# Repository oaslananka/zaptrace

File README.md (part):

<div align="center">

# ⚡ ZapTrace

### AI-native, verification-first EDA kernel for prompt-to-fab electronics.

**Prompt-to-Fab, with proofs.**<br />
Intent → normalized design → schematic → ERC → placement → routing → DRC → BOM → manufacturing package → auditable proof pack.

<p>

</p>

<p>

</p>

<p>
  <a href="https://oaslananka.github.io/zaptrace"><strong>Documentation</strong></a> ·
  <a href="#quickstart">Quickstart</a> ·
  <a href="docs/development/validation-environment.md">Validation Environment</a> ·
  <a href="ROADMAP.md">Roadmap</a> ·
  <a href="GOVERNANCE.md">Governance</a> ·
  <a href="SECURITY.md">Security</a> ·
  <a href="docs/SAFETY.md">Safety</a>
</p>

<p>
  
</p>

</div>

> [!WARNING]
> **Pre-1.0.** ZapTrace is a verification-first EDA kernel, not a fabrication guarantee. All generated outputs require human engineering review before fabrication or use. See [Safety Disclaimer](#safety-disclaimer).

> [!NOTE]
> **Proof Pack = evidence layer, not absolute correctness.** Proof packs record configured checks, artifacts, assumptions, and pass/fail evidence. A clean proof pack does not mean a board is manufacturer-approved, production-ready, or safe to fabricate without review.

---

## What ZapTrace Is

- **A Python SDK** for programmatic electronics design — parse, validate, place, route, export.
- **A CLI** (`zaptrace`) for quick design iteration from the terminal.
- **A local-first visual Studio** (`zaptrace studio`) for source-driven circuit exploration, linked component selection, preliminary board placement and safe YAML editing; not yet a full professional PCB CAD editor.
- **An MCP server** (`zaptrace-mcp`) whose default `expert` surface exposes 93 design tools plus 3 session-administration tools, with smaller task-oriented `inspect`, `design`, `verify`, `repair`, and `release` surfaces for bounded workflows.
- **A REST API** for web-based design workflows.
- **A verification engine** — Electrical Rule Checking (ERC) + Design Rule Checking (DRC) baked in.
- **A manufacturing export pipeline** — Gerber RS-274X, Excellon drill, BOM, pick-and-place, KiCad.
- **A proof-pack generator** — auditable, reproducible artifact bundles for every design.

## What ZapTrace Is Not

- ❌ **Not a full replacement for KiCad, Altium, or Eagle** — the initial Studio provides a live source and provisional-placement workspace, not full native CAD editing or manufacturing approval.
- ❌ **Not a general-purpose SPICE simulator or solver-grade sign-off tool** — ZapTrace can export SPICE and run bounded ngspice-backed evidence gates, but these do not replace full analog verification or qualified engineering review.
- ❌ **Not a replacement for human engineering judgment** — all outputs require review before fabrication.
- ❌ **Not fabrication-proven** — ZapTrace is pre-1.0. Manufacturing outputs are experimental.
- ❌ **Not fabrication-ready or production-ready** — no claim of fitness for manufacturing is made.
- ❌ **Proof Pack is not a correctness guarantee** — it is an evidence layer that records what was checked and what passed/failed. Absence of errors does not mean the design is correct or manufacturable.
- ❌ **KiCad Oracle (ERC/DRC) is external validation, not absolute correctness** — it catches rule violations the rules know about. A passing KiCad Oracle check does not guarantee a working circuit.
- ❌ **Fab profiles are not manufacturer approvals** — built-in profiles match common manufacturer capabilities, but you must verify against your specific manufacturer's current specifications. Always obtain pre-fabrication approval.
- ❌ **GitHub hardware CI cannot catch all hardware errors** — CI runs on simulated or limited hardware; physical validation (probe, power-up, functional test) is irreplaceable.

---

## Status

| Area | Status |
|------|--------|
| Design parsing | ✅ Implemented |
| Schematic synthesis | ⚠️ Template selection (keyword-matches a pre-built template; not from-scratch synthesis) |
| ERC (Electrical Rule Checking) | ✅ Implemented |
| Component placement | ✅ Implemented |
| Grid-based routing | ✅ Implemented |
| Net-aware smart routing | ✅ Implemented |
| DRC (Design Rule Checking) | ✅ Implemented |
| Net classification (EE knowledge) | ✅ Implemented |
| Copper pour generation | ✅ Implemented |
| Gerber RS-274X export | ✅ Implemented |
| Excellon drill export | ✅ Implemented |
| BOM (CSV + JSON) export | ✅ Implemented |
| Pick-and-place export | ✅ Implemented |
| KiCad schematic export | ✅ Implemented |
| KiCad hierarchical project import | ✅ Implemented |
| EasyEDA Standard import/export (round-trip ≥0.75) | ✅ Implemented (single flat JSON; import-only, no PCB editor) |
| EasyEDA Pro writer (import-only via KiCad) | ✅ Implemented (ZIP+JSONL; distinct from Standard) |
| Altium ASCII schematic import | ✅ Implemented (ASCII export only; OLE binary not supported) |
| SVG schematic rendering | ✅ Implemented |
| Manufacturing ZIP bundle | ✅ Implemented |
| MCP server (96 exposed tools: 93 design + 3 session administration) | ✅ Implemented |
| Power-tree architecture planner + netlist emit | ✅ Implemented |
| REST API server | ✅ Implemented |
| Design diff | ✅ Implemented |
| Full pipeline (autopilot) | ✅ Implemented |
| Proof-pack system | ✅ Implemented — evidence/sign-off foundation; not a correctness guarantee |
| Plugin system | 🚧 Experimental — signed runtime policy documented; production sandboxing still required |
| Review Studio | ✅ Implemented — human-review panels, proof-pack evidence, benchmark readiness |
| Live Code-to-Circuit Studio | 🧪 Initial local browser workspace — real YAML editing, source-linked connectivity/placement preview, save/undo and agent-aware revision tracking; native schematic editing and production CAD not yet supported |
| SPICE netlist export | ✅ Implemented foundation — DC gate is evidence/skip aware, not full analog sign-off |
| DFM (Design for Manufacturing) | ✅ Implemented foundation — fab profiles, manufacturing evidence, current/thermal/SI risk reports |
| Multi-board design | 🔮 Planned — post-0.3.0 |
| RF/microwave awareness | 🔮 Planned |

---

## v0.3.0 Release Scope

ZapTrace 0.3.0 is an evidence-hardening release. It adds bounded autonomous sign-off vocabulary, requirements coverage, assumption evidence, KiCad oracle evidence, manufacturing/DFM evidence, component/datasheet/footprint provenance, layout/power/SI/PI risk reports, known-failure benchmark mutation coverage, and Review Studio benchmark readiness panels.

This release still makes no fabrication-readiness claim. A pass means the configured evidence gates did not block; it does **not** mean the design is manufacturer-approved, production-ready, or safe to fabricate without human engineering review.

---

## Live Code-to-Circuit Studio

Open a real, editable ESP32 design example in a local browser workspace without manually exporting a static viewer:

**Development builds only for now:** the previously published PyPI 0.3.5 package does not include Studio.

```bash
zaptrace studio

# Or open an existing design.yaml directly (edits affect this file):
zaptrace studio --project path/to/design.yaml
```

Unsaved Studio YAML drafts can be recovered on a tab refresh when the browser retains tab session storage; they are never silently saved to the design file. If an agent changes the YAML while you have unsaved edits, **Compare versions** and **Download my draft** protect your work before you choose to load the agent's version. The **Following your source component** navigator links the selected YAML component to its exact Circuit, Board and illustrative 3D concept object, with keyboard focus and a return-to-source action; it never saves or invents unverified copper. **Double-click a component** in Circuit/Board/3D (or press **F2**) to edit its real YAML value; **Enter/Apply** saves and **Esc** cancels without writing. On first open, the **Start here** guide makes three real actions discoverable: select a source-linked component, trace a genuine net, or import your own YAML copy. It stays out of the way after a choice, is keyboard-accessible, and can be reopened from the header. Once Studio is running, choose **+ Open YAML copy** to select a local design in the browser without typing its path, or **Recent projects** to reopen a saved personal copy. Each import validates the source, opens in its own local session and leaves the original YAML untouched; the imported copy is an independent project, not synchronized back to the original. A running Studio also offers **Recent projects → Add Studio to your apps**, explicitly installing a local Linux Applications or Windows Start menu shortcut for later one-click launches, and **Quit desktop Studio** for app-menu-launched sessions. This uses the installed Python runtime (no Tauri/Electron or additional provider), and does not change desktop settings until clicked. Initial source installation still requires setup. The Studio keeps **one YAML file** as the authoritative design. On systems with KiCad installed, source-mapped resistors and capacitors show genuine local KiCad Device library artwork; selected ESP32/BME280/AMS1117 components can also display verified source-to-library pad matches in Inspector and jump into an interactive native pinout on the Circuit canvas for source-linked pin and net editing. The main Circuit cards also display local, source-matched KiCad ESP32/BME280/AMS1117 symbol artwork when available, with accurate mapped-pad coverage; cold library inspection runs after the fast YAML preview, never as a blocking prerequisite. Missing KiCad libraries keep the safe illustrative fallback. Partial source mappings are clearly reported and never treated as fabrication proof. Edit component values or nets in the code pane and see the corresponding source-linked logical schematic (including two-sided source pins, recognisable passive glyphs, and real net labels) update; select components, inspect source package pad mappings, and highlight logical net links across code and canvas, reassign a logical pin through Inspector or by selecting two schematic pins, trace real source net endpoints, explore board placement by dragging unrouted components, and use **Save design** to persist changes. Invalid drafts retain the last valid visual preview. An external agent/editor edit is detected without silently overwriting unsaved work. Use **↓ KiCad schematic** to download a real KiCad `.kicad_sch` from the current YAML draft (including unsaved net edits), with native KiCad wire segments/global net labels and embedded generated connectivity symbols; this does not save YAML or qualify ERC/DRC. The **3D concept** tab is now a source-linked, selectable isometric placement sketch of the actual board outline and component XY footprints; it does **not** assert native CAD 3D geometry, routed copper or physical validation. For the UI workflow and current engineering limitations, see [Studio user guide](docs/studio.md).

Source-backed pin-to-pin wire paths may now be drawn and adjusted within Studio and exported as real KiCad schematic segments; this is limited route geometry with unqualified generated symbols, not a full native schematic editor or verified copper.\n\nA local visual preview does **not** replace KiCad-native schematic, ERC, DRC, routing verification or qualified fabrication review.

## Quickstart

ZapTrace is pre-1.0. The registry distribution identity is `zaptrace-eda` while the Python import package and CLI remain `zaptrace`. `v0.3.5` is available on PyPI; its immutable tagged workflow failed the container-security gate before GitHub Release creation, so the tag is retained as partial-release evidence rather than rewritten. Active development has advanced to `0.3.6.dev0`. For a clean PyPI install of the latest published package:

```bash
uv venv --python 3.13
uv pip install "zaptrace-eda==0.3.5"
source .venv/bin/activate

# Run diagnostics
zaptrace doctor

# First run: scaffold a design locally (the published wheel does not
# contain the repository's examples/ directory).
zaptrace init sensor-demo --template esp32_i2c_sensor
zaptrace parse sensor-demo/design.yaml
zaptrace view sensor-demo/design.yaml --output sensor-demo/review

# Create KiCad/inspection outputs inside the working directory.
# Generation success does not mean ERC/DRC or fabrication readiness.
zaptrace pipeline --source sensor-demo/design.yaml --output sensor-demo/build
```

---

## CLI Usage

```bash
# Parse a design YAML
zaptrace parse design.yaml

# Inspect a parsed design
zaptrace inspect my_design

# Run ERC validation
zaptrace erc my_design

# List ERC rules
zaptrace erc-rules

# Place components
zaptrace place my_design

# Route nets
zaptrace route my_design

# Generate BOM
zaptrace bom my_design
zaptrace bom my_design --format json

# Generate design report
zaptrace report my_design --output report.md

# Render schematic SVG
zaptrace svg my_design --output schematic.svg

# Export to KiCad
zaptrace kicad my_design output/kicad/

# Diff two designs
zaptrace diff design_a design_b

# Search library
zaptrace library search resistor
zaptrace library get 0402_10k

# Run full pipeline
zaptrace pipeline --source design.yaml --output build/
zaptrace pipeline --intent "ESP32 I2C sensor node"
```

---

## Python SDK Usage

```python
from zaptrace.core.parser import parse_file
from zaptrace.erc.runner import ERCRunner
from zaptrace.algo.placer import place_components
from zaptrace.algo.router import route_design_smart
from zaptrace.export.manufacturing import generate_manufacturing_bundle
from zaptrace.ee.classifier import classify_design

# Parse
design = parse_file("design.yaml")

# Validate
runner = ERCRunner()
erc_result = runner.run(design)

# Classify nets
classify_design(design)

# Place & route
positions = place_components(design)
routing, route_result = route_design_smart(design, positions)

# Export
bundle = generate_manufacturing_bundle(design, "build/")
print(f"Gerber layers: {list(bundle['gerber_layers'].keys())}")
```

---

## MCP Usage

ZapTrace exposes an MCP server for AI agent integration.

```bash
# Start MCP server (stdio mode)
zaptrace-mcp

# Start MCP server (HTTP loopback mode)
zaptrace-mcp-http
```

Configure in your AI client's MCP settings:

```json
{
  "mcpServers": {
    "zaptrace": {
      "command": "zaptrace-mcp"
    }
  }
}
```

See [MCP quickstart](docs/mcp/quickstart.md) for the tool catalog and [agent plugin publication](docs/agent-plugin-publication.md) for product-owned skills, runtime boundaries, and activation gates.

---

## REST API Usage

```bash
# Start the secure loopback server on 127.0.0.1:8080.
zaptrace-api

# Health does not require a bearer token.
curl http://127.0.0.1:8080/health
```

For the authenticated REST and MCP HTTP Compose deployment, copy `.env.example`, set both token values, and run `docker compose up --build --wait`. See [REST API production hardening](docs/api-rest-production.md) and [MCP HTTP deployment](docs/mcp-http-deployment.md).

---

## Manufacturing Export

ZapTrace generates all files needed for PCB fabrication:

| Artifact | Format | Status |
|----------|--------|--------|
| Copper layers | Gerber RS-274X | ✅ |
| Drill file | Excellon | ✅ |
| Bill of Materials | CSV / JSON | ✅ |
| Pick-and-place | CSV | ✅ |
| Manufacturing bundle | ZIP | ✅ |
| KiCad project | .kicad_pcb, .kicad_sch | ✅ |
| Schematic | SVG | ✅ |
| Design report | Markdown | ✅ |

```bash
# Generate everything
zaptrace export manufacturing my_design --output build/board
```

---

## Proof Pack

A Proof Pack is an auditable, reproducible artifact bundle that explains what ZapTrace generated and why.

```bash
zaptrace proof-pack design.yaml --output build/proof-pack
```

Each proof pack contains:
- Design inputs and normalized model
- ERC results (what was checked and what passed/failed)
- DRC results
- BOM and supply-chain overview
- All manufacturing artifacts
- Decision log
- Reproducibility metadata
- Warnings and review checklist

See [docs/strategy/proof-pack-spec.md](docs/strategy/proof-pack-spec.md) for details.

---

## Verification Model

ZapTrace uses a layered verification model. Each layer produces evidence; none is a correctness guarantee.

### Evidence Layers

| Layer | What It Does | What It Does NOT Do |
|-------|-------------|---------------------|
| **Parser** | Validates design YAML structure and constraints | Does not verify circuit functionality |
| **ERC (29 rules)** | Checks electrical rules (net connectivity, pin compatibility, power, power-tree, DNP-aware) | Does not simulate the circuit or verify timing |
| **DRC (16 rules)** | Checks physical design rules (clearance, width, drill) | Does not guarantee manufacturability |
| **KiCad Oracle** | Exports to KiCad and runs KiCad's ERC/DRC as external validation | KiCad may have different rules; a pass does not mean the design is correct |
| **Proof Pack** | Records all verification results, artifact hashes, environment metadata, and decisions | Evidence of what was checked, not a guarantee of correctness |
| **Fab Profiles** | Documents manufacturer capabilities (min trace, min drill, layers) | Not a manufacturer approval; always verify with your fab house |
| **GitHub Hardware CI** | Runs hardware-level integration checks on available runners | Cannot reproduce all real-world hardware conditions; physical testing required |

### What "Verification-First" Means

- Verification is **built into the pipeline**, not bolted on after export.
- Every design artifact has an auditable chain: who checked what, with which tool, and what result.
- The design pipeline stops on hard errors (ERC/DRC failures) and requires explicit override.
- **Human engineering review is mandatory** before fabrication. No automated tool can replace domain expertise.

### Non-Claims

ZapTrace does **not** claim:

- **Fabrication-ready** — no automated verification pipeline can guarantee a board will fabricate correctly.
- **Production-ready** — pre-1.0; APIs and outputs may change.
- **Manufacturer-approved** — fab profiles are reference configurations, not approvals.
- **Guaranteed correctness** — all verification tools have blind spots.
- **Fully automatic manufacturing** — every manufacturing output requires human review and fab house approval.

---

## Architecture

```mermaid
graph TD
    A[YAML Design File] --> B[Parser]
    A1[Natural Language Intent] --> B1[Synthesis Engine]
    B1 --> B

    B --> C[Design Model<br/>Pydantic]
    C --> D[EE Knowledge<br/>Classifier]

    D --> E[ERC Engine]
    E --> F{RC Passed?}

    F -->|Yes| G[Placer]
    F -->|No| H[Suggest Patches]
    H --> C

    G --> I[Router]
    I --> J[DRC Engine]

    J --> K{DRC Passed?}
    K -->|Yes| L[Export Pipeline]
    K -->|No| I

    L --> M[Gerber]
    L --> N[Excellon]
    L --> O[BOM]
    L --> P[Pick-and-Place]
    L --> Q[KiCad]
    L --> R[SVG Schematic]

    L --> S[Proof Pack Generator]
    S --> T[manifest.json + artifacts]

    C --> U[MCP Server]
    C --> V[REST API]
    C --> W[CLI]
```

---

## Example Gallery

| Example | Description |
|---------|-------------|
| [ESP32 I2C Sensor Node](examples/esp32_i2c_sensor_node/) | ESP32-C3 reading temperature/humidity over I2C |
| [RP2040 USB HID](examples/rp2040_usb_hid/) | RP2040-based USB keyboard controller |
| [USB-C LiPo Charger](examples/usb_c_lipo_charger/) | USB-C powered LiPo charger with protection |
| [STM32 RS485 Node](examples/stm32_rs485_node/) | Industrial STM32 RS485 Modbus node |
| [nRF52840 BLE Sensor](examples/nrf52840_ble_sensor/) | BLE environmental sensor with nRF52840 |

See [examples/](examples/) for design YAML files and walkthroughs.

---

## Safety Disclaimer

> **⚠️ ELECTRONICS DESIGN IS INHERENTLY RISKY.**
>
> ZapTrace is pre-1.0 software. All outputs — schematics, layouts, manufacturing files — **must be reviewed by a qualified electrical engineer before fabrication or use**.
>
> Incorrect PCB designs can cause:
> - Fire or thermal damage
> - Equipment damage
> - Electrical shock
> - Radio interference (legal liability)
> - Complete system failure
>
> ZapTrace is provided as-is, without warranty of any kind. The maintainers assume no liability for damages arising from the use of this software or its outputs.
>
> **Verification tools are evidence layers, not correctness guarantees.**
> - A passing ERC/DRC/KiCad Oracle check does not mean the design is correct or manufacturable.
> - A valid Proof Pack attests what was checked, not that the design is safe.
> - GitHub hardware CI cannot replace physical testing.
> - Fab profiles are reference configurations, not manufacturer approvals.
>
> **If you are not an electrical engineer, consult one before fabricating any ZapTrace-generated design.**
>
> See [docs/SAFETY.md](docs/SAFETY.md) for the full safety policy.

---

## Persistent local state

Controlled deployments can persist committed designs, immutable version lineage, snapshots, transactions, audit events, object ACLs, and evidence identities in local SQLite:

```bash
export ZAPTRACE_SESSION_STORE_ROOT="$HOME/.local/share/zaptrace/state"
zaptrace-mcp
```

Persistence is opt-in; unset deployments retain process-local behavior. Isolated workers cannot write durable state directly, active proof/release references protect artifacts from retention cleanup, and startup fails closed on schema or integrity errors. See [Persistent versioned state](docs/storage/persistent-state.md) for backup, restore, migration, deployment modes, and non-claims.

---

## Roadmap

| Horizon | Focus |
|---------|-------|
| **Legacy baseline (v0.3.3)** | PyPI-only release without public Git provenance; preserved as immutable historical evidence |
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
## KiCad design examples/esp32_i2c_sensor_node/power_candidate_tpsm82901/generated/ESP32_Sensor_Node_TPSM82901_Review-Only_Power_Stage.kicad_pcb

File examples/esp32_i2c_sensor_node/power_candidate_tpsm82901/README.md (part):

# TPSM82901SISR review-only power-stage candidate

**Status: isolated four-layer review candidate — routed and native DRC/ERC clean, but not electrically bench-tested, thermally/EMI-qualified or approved for fabrication. It is not part of the active ESP32 source design.**

This isolated KiCad project evaluates a lower-loss 5 V → 3.3 V buck replacement for the current AMS1117 placeholder. It is intentionally separate from examples/esp32_i2c_sensor_node/design.yaml. It contains a first-pass compact power-stage placement, copper zones, short signal paths and stitching vias; it remains an engineering candidate, not a released board design.

## Exact device and pin contract

- Production orderable MPN: TPSM82901SISR (TI product addendum dated 2026-02-06 lists it Active / Production; uSiP SIS, 11 pins).
- Package: SIS0011A, 3.0 × 2.8 × 1.6 mm max, integrated 1 µH inductor.
- Pins: 1/2 VIN; 3 EN; 4 MODE/S-CONF; 5 SS/TR; 6 PG; 7 FB/VSET; 8 SW/NC; 9/10 VOUT; 11 exposed GND.
- Pin 8 is intentionally floating (no net, no copper). Pin 11 must be soldered to the common ground plane.
- The 11-pad local footprint is explicitly marked DRAFT and is not promoted into ZapTrace's verified vendor-footprint registry. It now follows TI SIS0011A example dimensions: ten 0.55 mm-long perimeter lands; four corner lands 0.575 mm wide and six middle lands 0.25 mm wide; inner-pin pitch 0.5 mm; outer pin 1-to-5 / 10-to-6 span 2.325 mm; center exposed land 0.9 × 2.15 mm. The footprint uses TI's solder-mask-defined example (nominal 0.05 mm mask encroachment) and two split stencil windows approximating 80% paste coverage. The stencil split is an approximation from the datasheet image and requires assembly review. The drawing marks three optional 0.2 mm via locations under the exposed land; they are deliberately not drilled in this draft because TI requires vias beneath paste to be filled, plugged or tented, and the assembly process is not yet defined.

## Electrical configuration (TI TPSM82901EVM BSR188-001 reference)

| Ref | Value / connection | Function |
|---|---|---|
| U3 | TPSM82901SISR | 3.3 V buck |
| C1 | 10 µF, 25 V, X7R, TDK C3216X7R1E106K160AE | VIN bypass candidate |
| C2 | 22 µF, 10 V, X7S, TDK C2012X7S1A226M125AC | VOUT capacitance candidate |
| R1 | 113 kΩ, 1% | VOUT-to-FB upper divider |
| R2 | 24.9 kΩ, 1% | FB-to-GND lower divider |
| R3 | 7.15 kΩ, 1% to GND | 2.5 MHz, Auto PFM/PWM with AEE, external FB, output discharge disabled |
| C3 | 22 pF, C0G | Optional feed-forward capacitor |
| C4 | 3.3 nF | SS/TR capacitor (EVM value) |
| R4 | 1 MΩ | PG open-drain pull-up to VOUT |

Nominal feedback calculation: 0.6 × (1 + 113 kΩ / 24.9 kΩ) = 3.3229 V. This is the nominal resistor-ratio target using the 0.6 V feedback reference; it is not a measurement. The TI EVM uses the same nominal 3.3 V output. The selected capacitor MPNs are candidate parts only: confirm effective capacitance at applied DC bias, tolerance, temperature and aging before approving the circuit.

## Layout status

The candidate board is set to four copper layers: F.Cu, In1.Cu, In2.Cu and B.Cu. A broad GND zone is present on all four layers; VIN and VOUT have local top-layer copper regions and In1.Cu spreading islands. CIN is next to VIN, COUT next to VOUT, the FB divider/CFF are close to FB, the MODE resistor faces MODE/S-CONF and the SS capacitor faces SS/TR. The first-pass layout contains 15 copper track segments and 11 through-vias (0.60 mm copper / 0.30 mm finished drill). One additional GND stitching via at (20.0, 15.8) connects the exposed-pad-side GND copper to the inner/bottom planes; it remains outside the exposed pad and stencil apertures (not via-in-pad). The boundary VIN/3V3 feeds, local signal routes, PG return and power/GND zone fills are connected. All designators remain visible on KiCad F.Fab for review; they are not placed on F.Silkscreen, keeping the switching-power area and solder-mask clear. Native KiCad reports zero unconnected items. This is a first-pass topology/layout candidate; copper distribution and the 4-layer GND reference still require detailed EMI, transient, current-density and thermal review. The KiCad board records 1.6 mm overall thickness and four copper layers, but does not specify a copper weight/finished copper thickness. TI recommends 1 oz copper for its thermal guidance; this candidate does not yet prove that condition or inherit the TI EVM/JEDEC thermal resistance.

TI states that SW/NC must remain floating; any copper beneath it must be small, electrically floating, isolated from inner layers and have no vias. Pad 8 has no net, and an all-copper-layer rule area blocks tracks, vias and zone fills beneath/around the package pad. The DRC report shows no items in that keepout.

## Power budget and integration review — 2026-11-03

### Capacitor sufficiency

TI specifies at least **3 µF effective input capacitance** and, at the selected
2.5 MHz mode, at least **10 µF effective output capacitance** directly at the
device. Its application guidance recommends 10 µF nominal at VIN for most
applications and 22 µF nominal at VOUT. The selected 10 µF / 22 µF parts match
those nominal starting values, but nominal marking is not the same as
effective capacitance. TDK publishes DC-bias characteristic curves for both
selected MPNs; the exact effective values at 5 V VIN and 3.323 V VOUT,
including tolerance and temperature, have not yet been extracted or measured.
Do not mark either minimum as proven until those curves or bench measurements
are checked against TI's effective-capacitance limits.

The EVM adds a 47 µF tantalum bulk input capacitor in addition to its 10 µF
MLCC. TI's datasheet does not make that extra 47 µF mandatory for most
applications. Do not add it automatically; decide from the actual USB source,
cable impedance and input-transient measurements.

### 5 V source-current envelope

For a buck converter, the first-order input estimate is
I_IN = V_OUT × I_OUT / (V_IN × efficiency). At 5 V input and 3.3 V output:

| 3.3 V output load | Assumed efficiency | Estimated 5 V input |
|---:|---:|---:|
| 379 mA | 80% | 313 mA |
| 379 mA | 85% | 294 mA |
| 379 mA | 90% | 278 mA |
| 500 mA | 80% | 413 mA |
| 500 mA | 85% | 388 mA |
| 500 mA | 90% | 367 mA |
| 1,000 mA | 85% | 776 mA |

These efficiencies are illustrative assumptions, **not measured TPSM82901
efficiency at 5 V / 3.3 V**. Espressif's 500 mA recommendation is a minimum
source-capability recommendation, not a measured constant ESP32 current.
Sensors and other 3.3 V loads add to the module's demand. The TPSM82901's 1 A
rating therefore does not mean the USB-powered board may draw 1 A from a
default-current USB-C source.

The Type-C sink in the active source schematic has 5.1 kΩ CC pull-downs, but
no current-advertisement sensing/limit logic is represented. Treat default
source capability as the design envelope unless a compliant source-current
detection/management design is added separately. Do not assume a 1.5 A or
3 A source just because the connector is USB-C.

### Board-level ESP32 integration findings

The active source design was inspected but not changed:
- USB-C VBUS entry currently has a 100 nF capacitor (C3) and the PESD5V0S1BA
  protection element (D1), but no 10 µF nominal bulk capacitor at the main
  power entrance. The buck candidate's 10 µF C1 is local to the converter;
  it is not at the USB-C entry after integration because the source design
  places U3 about 34 mm from J1.
- The source design's 10 µF 3.3 V capacitor C2 is approximately 26.9 mm from
  the ESP32 module U1; its 100 nF C1 is approximately 26 mm away. Espressif
  recommends local 10 µF support on VDD3P3 and an additional 10 µF at the main
  power entrance when those locations are not close. On this board, they are
  not close.
- The isolated buck candidate's C2 is a local converter output capacitor;
  it does not replace the ESP32 module's local bypass capacitor.

These are integration requirements to review before adopting the buck.
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
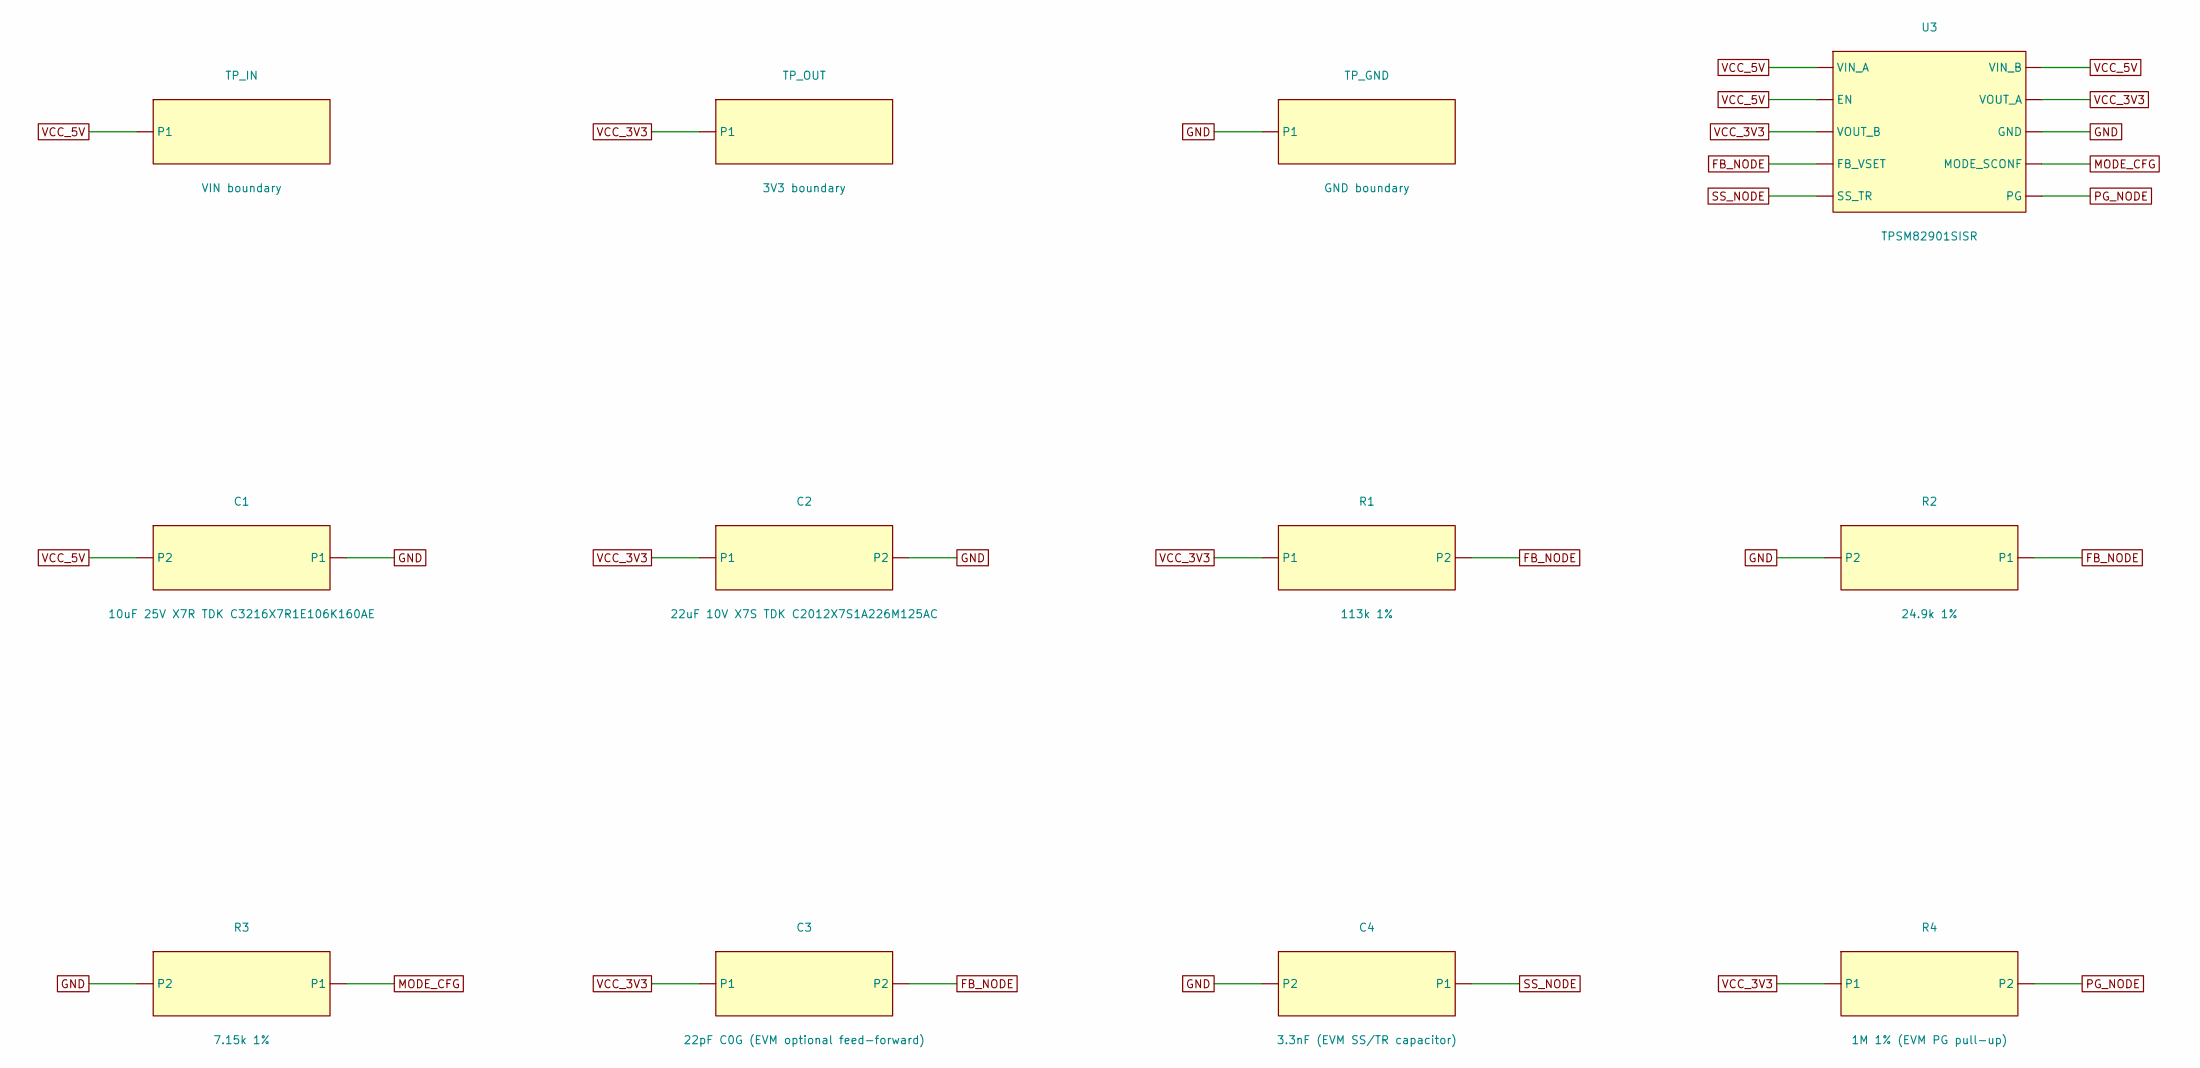
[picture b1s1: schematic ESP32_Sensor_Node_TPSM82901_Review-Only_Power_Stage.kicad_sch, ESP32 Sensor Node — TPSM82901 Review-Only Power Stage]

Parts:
C1: 10uF 25V X7R TDK C3216X7R1E106K160AE; C_1206_3216Metric
C2: 22uF 10V X7S TDK C2012X7S1A226M125AC; C_0805_2012Metric
C3: 22pF C0G (EVM optional feed-forward); C_0603_1608Metric
C4: 3.3nF (EVM SS/TR capacitor); C_0603_SS_Rev
R1: 113k 1%; R_0603_1608Metric
R2: 24.9k 1%; R_0603_1608Metric
R3: 7.15k 1%; R_0603_Mode_Rev
R4: 1M 1% (EVM PG pull-up); R_0603_1608Metric
TP_GND: GND boundary; TestPoint_Pad_D1.0mm
TP_IN: VIN boundary; TestPoint_Pad_D1.0mm
TP_OUT: 3V3 boundary; TestPoint_Pad_D1.0mm
U3: TPSM82901SISR; TPSM82901

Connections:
FB_NODE: C3.2, R1.2, R2.1, U3.7 (FB_VSET)
GND: C1.1, C2.2, C4.2, R2.2, R3.2, TP_GND.1, U3.11 (GND)
MODE_CFG: R3.1, U3.4 (MODE_SCONF)
PG_NODE: R4.2, U3.6 (PG)
SS_NODE: C4.1, U3.5 (SS_TR)
VCC_3V3: C2.1, C3.1, R1.1, R4.1, TP_OUT.1, U3.9 (VOUT_A), U3.10 (VOUT_B)
VCC_5V: C1.2, TP_IN.1, U3.1 (VIN_A), U3.2 (VIN_B), U3.3 (EN)

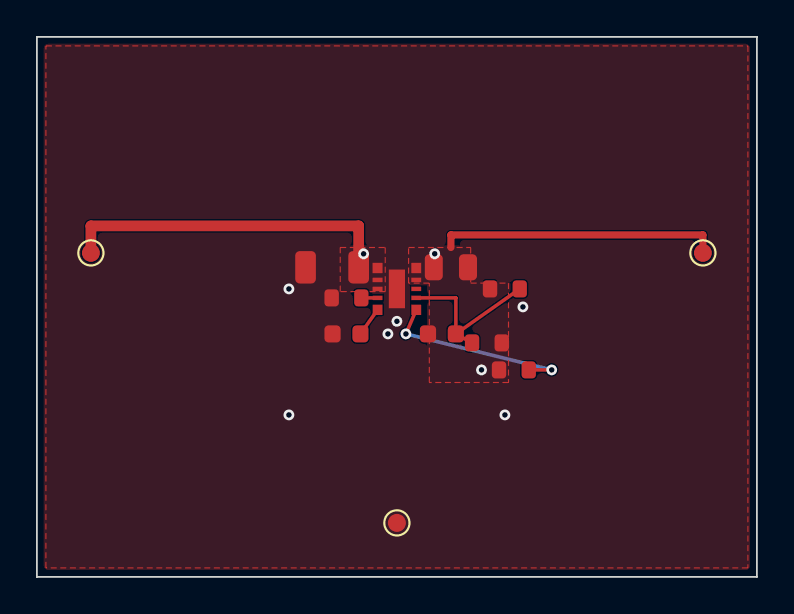
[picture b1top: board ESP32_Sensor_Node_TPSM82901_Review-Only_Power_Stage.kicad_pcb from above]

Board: 4 copper layers, 40.0 x 30.0 mm, 12 parts (0 on the bottom side), 7 nets.

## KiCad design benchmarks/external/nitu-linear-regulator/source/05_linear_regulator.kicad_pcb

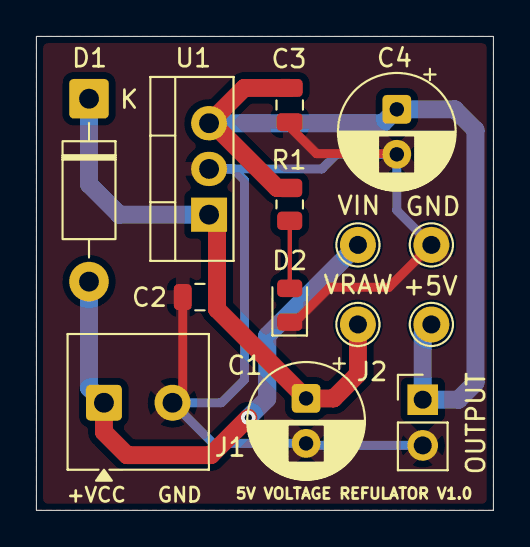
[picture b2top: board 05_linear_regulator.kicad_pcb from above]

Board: 2 copper layers, 25.4 x 26.3 mm, 14 parts (0 on the bottom side), 5 nets.

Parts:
+5V: +5V; TestPoint_THTPad_D2.0mm_Drill1.0mm
C1: 100uF 25V; CP_Radial_D6.3mm_P2.50mm
C2: 1uF; C_0805_2012Metric
C3: 100nF; C_0805_2012Metric
C4: 100uF 16V; CP_Radial_D6.3mm_P2.50mm
D1: 1N5819; D_DO-41_SOD81_P10.16mm_Horizontal
D2: RED; LED_0805_2012Metric
GND: GND; TestPoint_THTPad_D2.0mm_Drill1.0mm
J1: INPUT; TerminalBlock_Phoenix_MKDS-1-2-3.81_1x02_P3.81mm_Horizontal
J2: OUTPUT; PinHeader_1x02_P2.54mm_Vertical
R1: 330; R_0805_2012Metric
U1: L7805; TO-220-3_Vertical
VIN: Vin; TestPoint_THTPad_D2.0mm_Drill1.0mm
VRAW: Vraw; TestPoint_THTPad_D2.0mm_Drill1.0mm

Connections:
+5V: +5V.1 (1_1), C3.1, C4.1, J2.1, R1.1, U1.3 (OUT)
/VIN: D1.2 (A), J1.1, VIN.1 (1_1)
/VRAW: C1.1, C2.1, D1.1 (K), U1.1 (IN), VRAW.1 (1_1)
GND: C1.2, C2.2, C3.2, C4.2, D2.1 (K), GND.1 (1_1), J1.2, J2.2, U1.2 (GND)
unnamed: D2.2 (A), R1.2

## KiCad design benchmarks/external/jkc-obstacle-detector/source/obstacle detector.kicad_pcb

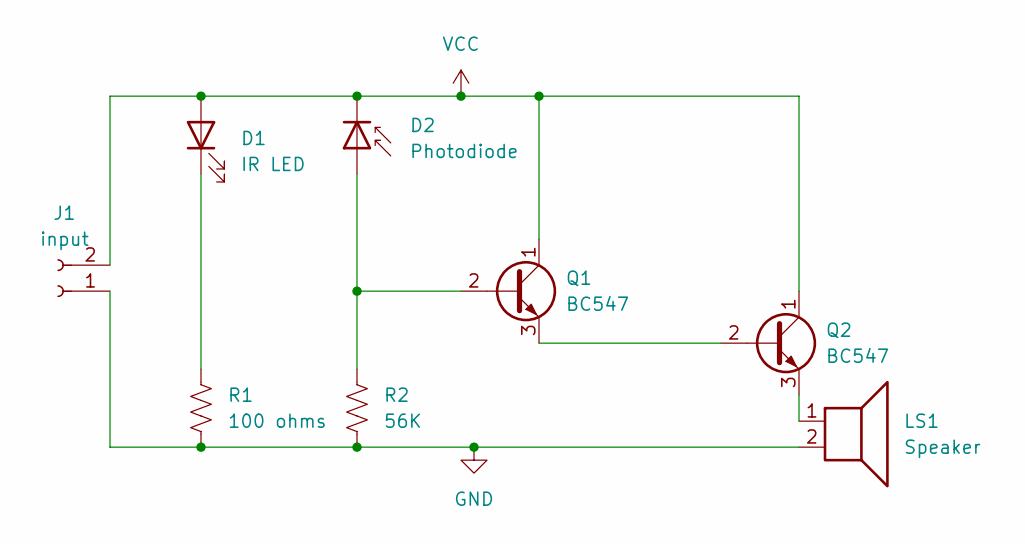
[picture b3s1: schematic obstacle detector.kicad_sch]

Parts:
D1: IR LED; LED_D5.0mm_Clear
D2: Photodiode; LED_D5.0mm_IRBlack
J1: input; TerminalBlock_Phoenix_MKDS-1,5-2_1x02_P5.00mm_Horizontal
LS1: Speaker; Buzzer_12x9.5RM7.6
Q1, Q2: BC547; TO-92_Inline
R1: 100 ohms; R_Axial_DIN0207_L6.3mm_D2.5mm_P7.62mm_Horizontal
R2: 56K; R_Axial_DIN0207_L6.3mm_D2.5mm_P7.62mm_Horizontal

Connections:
GND: J1.1, LS1.2, R1.2, R2.2
unnamed: D1.1 (K), R1.1
unnamed: D2.2 (A), Q1.2 (B), R2.1
unnamed: Q1.3 (E), Q2.2 (B)
unnamed: LS1.1, Q2.3 (E)
VCC: D1.2 (A), D2.1 (K), J1.2, Q1.1 (C), Q2.1 (C)

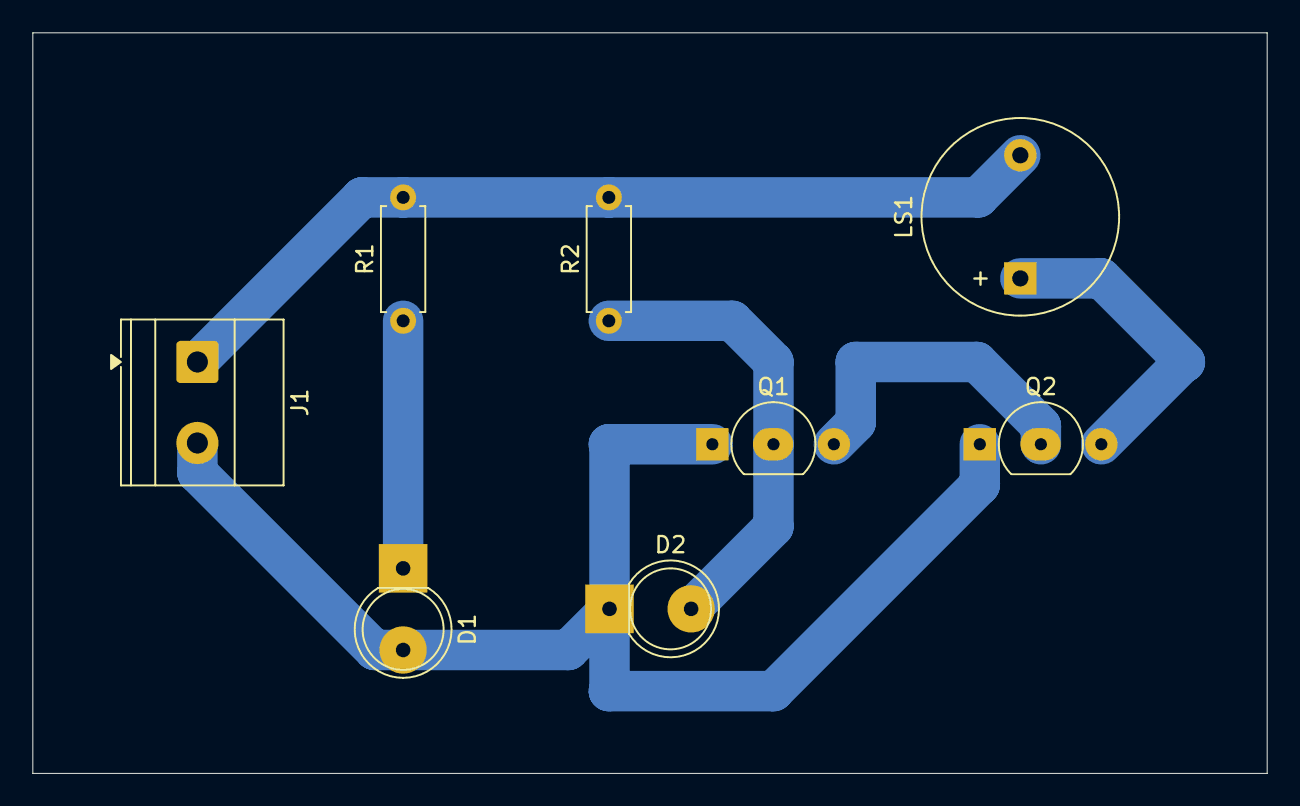
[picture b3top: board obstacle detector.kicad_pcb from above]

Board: 2 copper layers, 76.2 x 45.7 mm, 8 parts (0 on the bottom side), 6 nets.

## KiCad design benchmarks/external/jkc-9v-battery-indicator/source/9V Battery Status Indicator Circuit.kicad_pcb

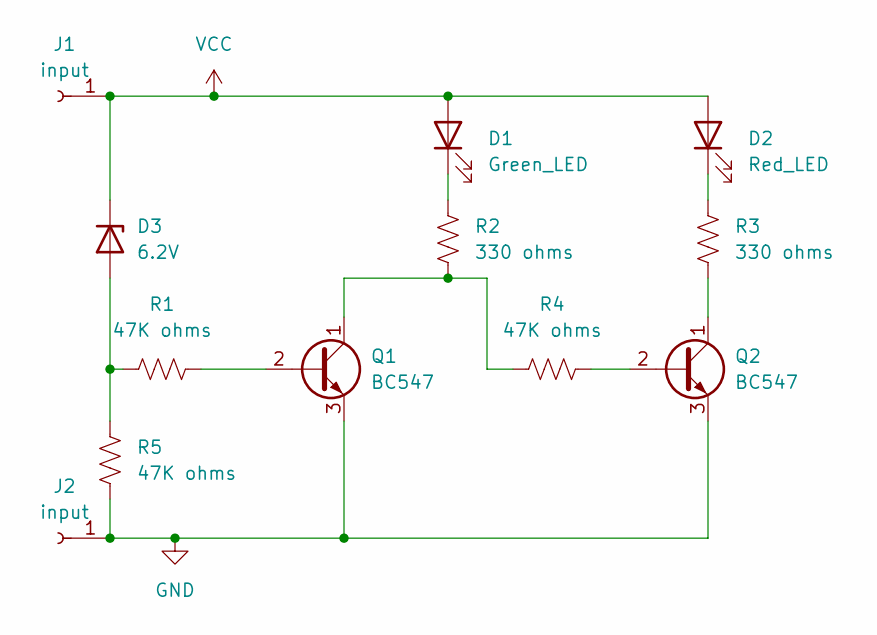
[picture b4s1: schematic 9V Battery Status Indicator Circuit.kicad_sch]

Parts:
D1: Green_LED; LED_D5.0mm
D2: Red_LED; LED_D5.0mm
D3: 6.2V; D_A-405_P7.62mm_Horizontal
J1, J2: input; PinSocket_1x01_P2.54mm_Horizontal
Q1, Q2: BC547; TO-92_Inline
R1, R4, R5: 47K ohms; R_Axial_DIN0207_L6.3mm_D2.5mm_P10.16mm_Horizontal
R2, R3: 330 ohms; R_Axial_DIN0207_L6.3mm_D2.5mm_P10.16mm_Horizontal

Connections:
GND: J2.1 (Pin_1_1), Q1.3 (E), Q2.3 (E), R5.2
unnamed: D1.1 (K), R2.1
unnamed: D2.1 (K), R3.1
unnamed: D3.2 (A), R1.1, R5.1
unnamed: Q1.2 (B), R1.2
unnamed: Q1.1 (C), R2.2, R4.1
unnamed: Q2.2 (B), R4.2
unnamed: Q2.1 (C), R3.2
VCC: D1.2 (A), D2.2 (A), D3.1 (K), J1.1 (Pin_1_1)

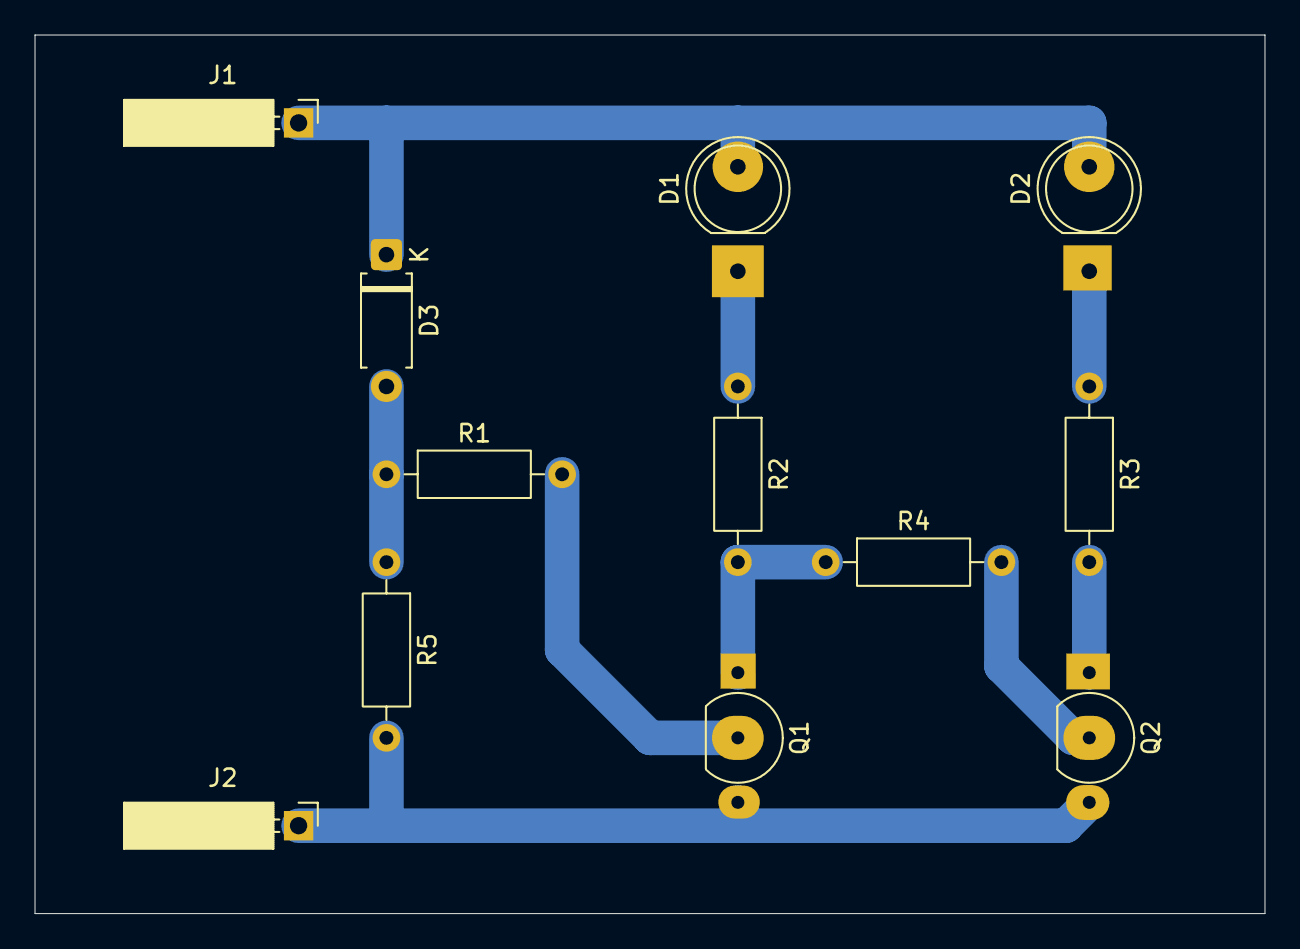
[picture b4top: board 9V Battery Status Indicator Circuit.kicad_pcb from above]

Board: 2 copper layers, 71.1 x 50.8 mm, 12 parts (0 on the bottom side), 9 nets.

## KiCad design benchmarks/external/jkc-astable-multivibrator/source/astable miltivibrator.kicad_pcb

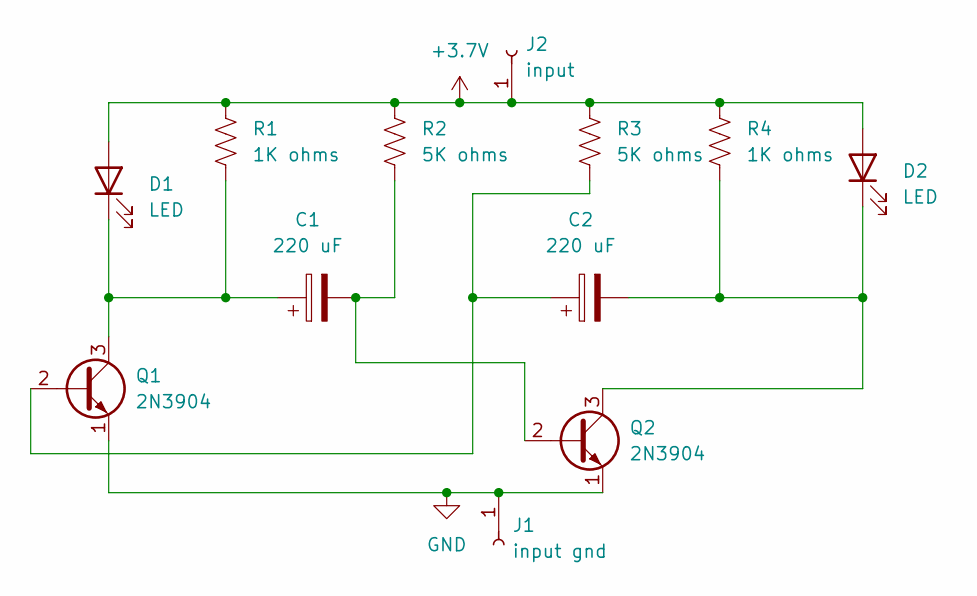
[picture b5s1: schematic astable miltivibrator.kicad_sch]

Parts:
C1, C2: 220 uF; CP_Radial_D10.0mm_P3.50mm
D1, D2: LED; LED_D5.0mm
J1: input gnd; PinSocket_1x01_P2.54mm_Horizontal
J2: input; PinSocket_1x01_P2.54mm_Horizontal
Q1, Q2: 2N3904; TO-92_Inline
R1, R4: 1K ohms; R_Axial_DIN0207_L6.3mm_D2.5mm_P7.62mm_Horizontal
R2, R3: 5K ohms; R_Axial_DIN0207_L6.3mm_D2.5mm_P7.62mm_Horizontal

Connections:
+3.7V: D1.2 (A), D2.2 (A), J2.1 (Pin_1_1), R1.1, R2.1, R3.1, R4.1
GND: J1.1 (Pin_1_1), Q1.1 (E), Q2.1 (E)
unnamed: C1.1, D1.1 (K), Q1.3 (C), R1.2
unnamed: C2.2, D2.1 (K), Q2.3 (C), R4.2
unnamed: C2.1, Q1.2 (B), R3.2
unnamed: C1.2, Q2.2 (B), R2.2

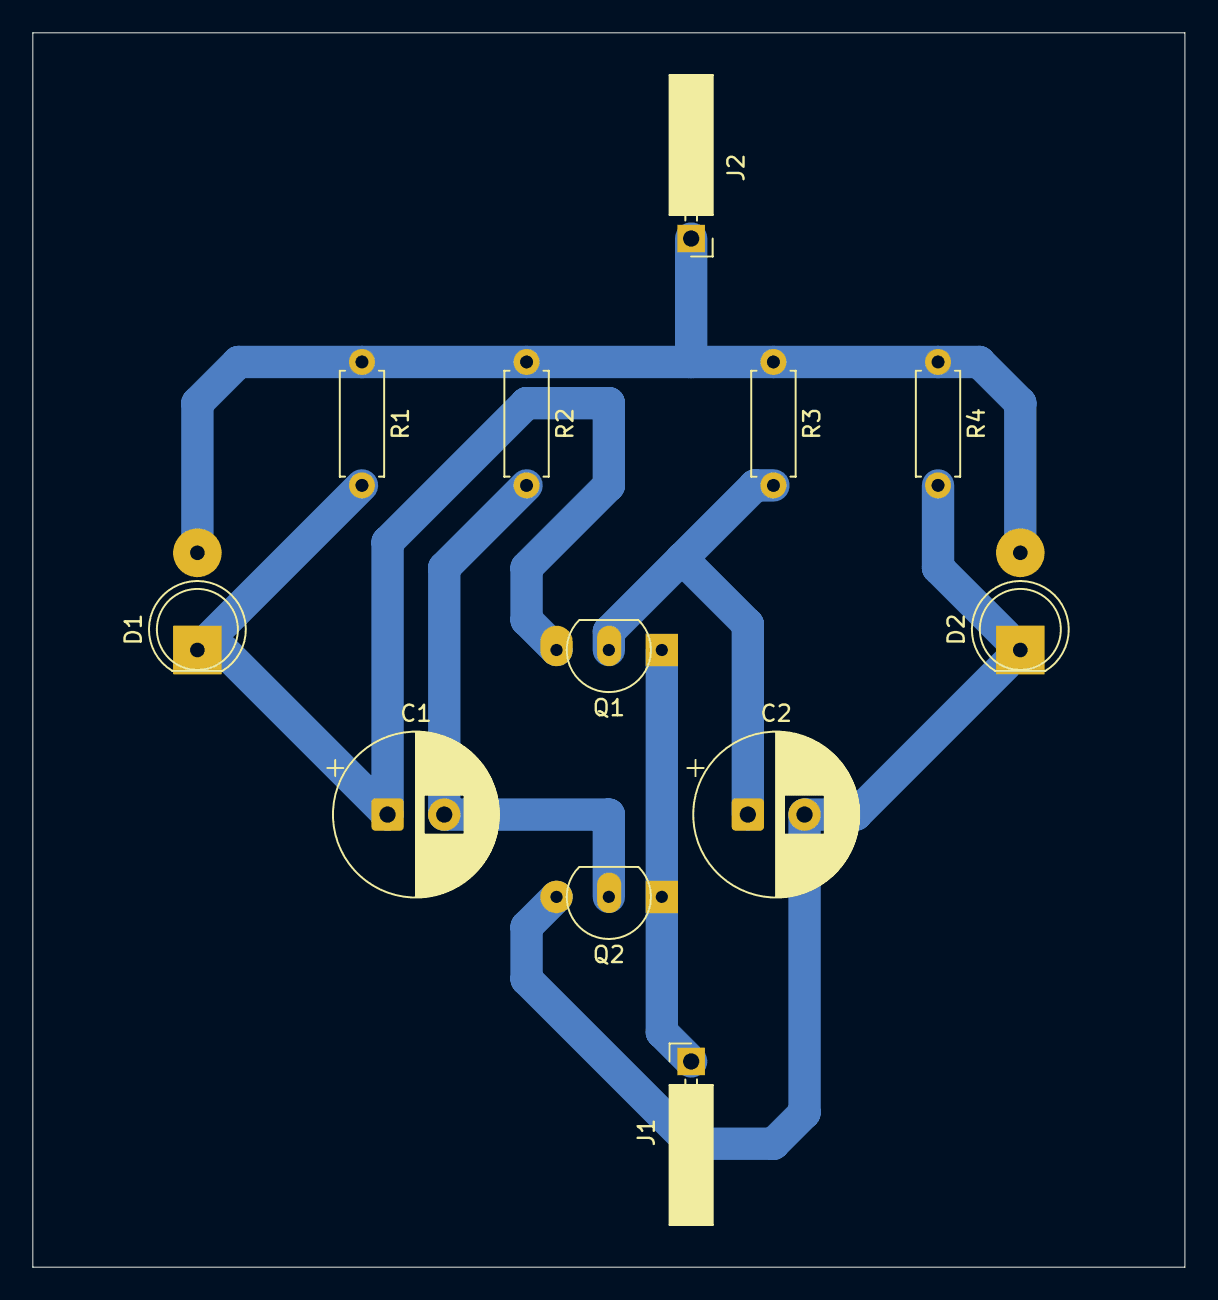
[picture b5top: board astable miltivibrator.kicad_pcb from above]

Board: 2 copper layers, 71.1 x 76.2 mm, 12 parts (0 on the bottom side), 6 nets.

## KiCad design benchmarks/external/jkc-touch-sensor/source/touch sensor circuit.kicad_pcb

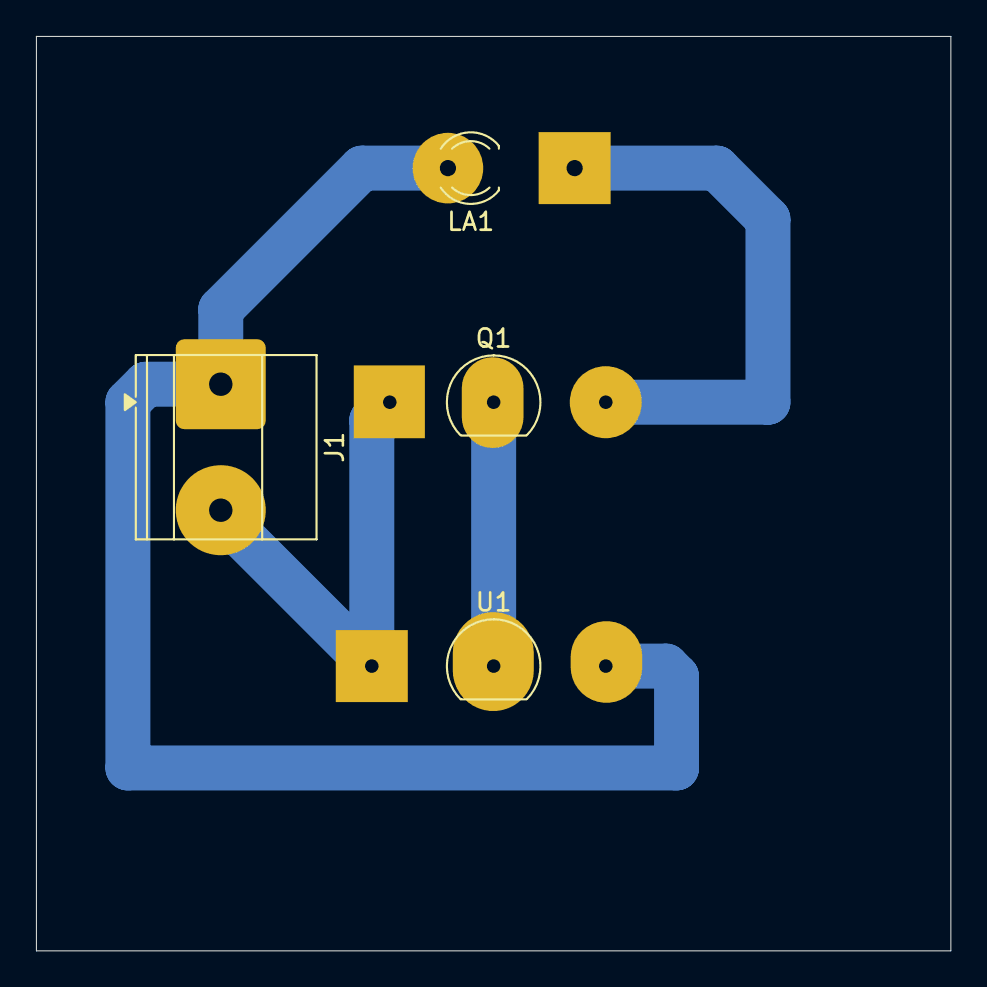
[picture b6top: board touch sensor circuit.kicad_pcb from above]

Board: 2 copper layers, 50.8 x 50.8 mm, 4 parts (0 on the bottom side), 4 nets.

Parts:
J1: Conn_01x02_Socket; TerminalBlock_Phoenix_MKDS-1,5-2_1x02_P5.00mm_Horizontal
LA1: Lamp; LED_D3.0mm
Q1: BC547; TO-92_Inline
U1: touch sensor; TO-92_Inline

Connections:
unnamed: J1.1, LA1.2 (+), U1.2 (GND)
unnamed: J1.2, Q1.1 (C), U1.1 (VCC)
unnamed: LA1.1 (-), Q1.3 (E)
unnamed: Q1.2 (B), U1.3 (OUT)

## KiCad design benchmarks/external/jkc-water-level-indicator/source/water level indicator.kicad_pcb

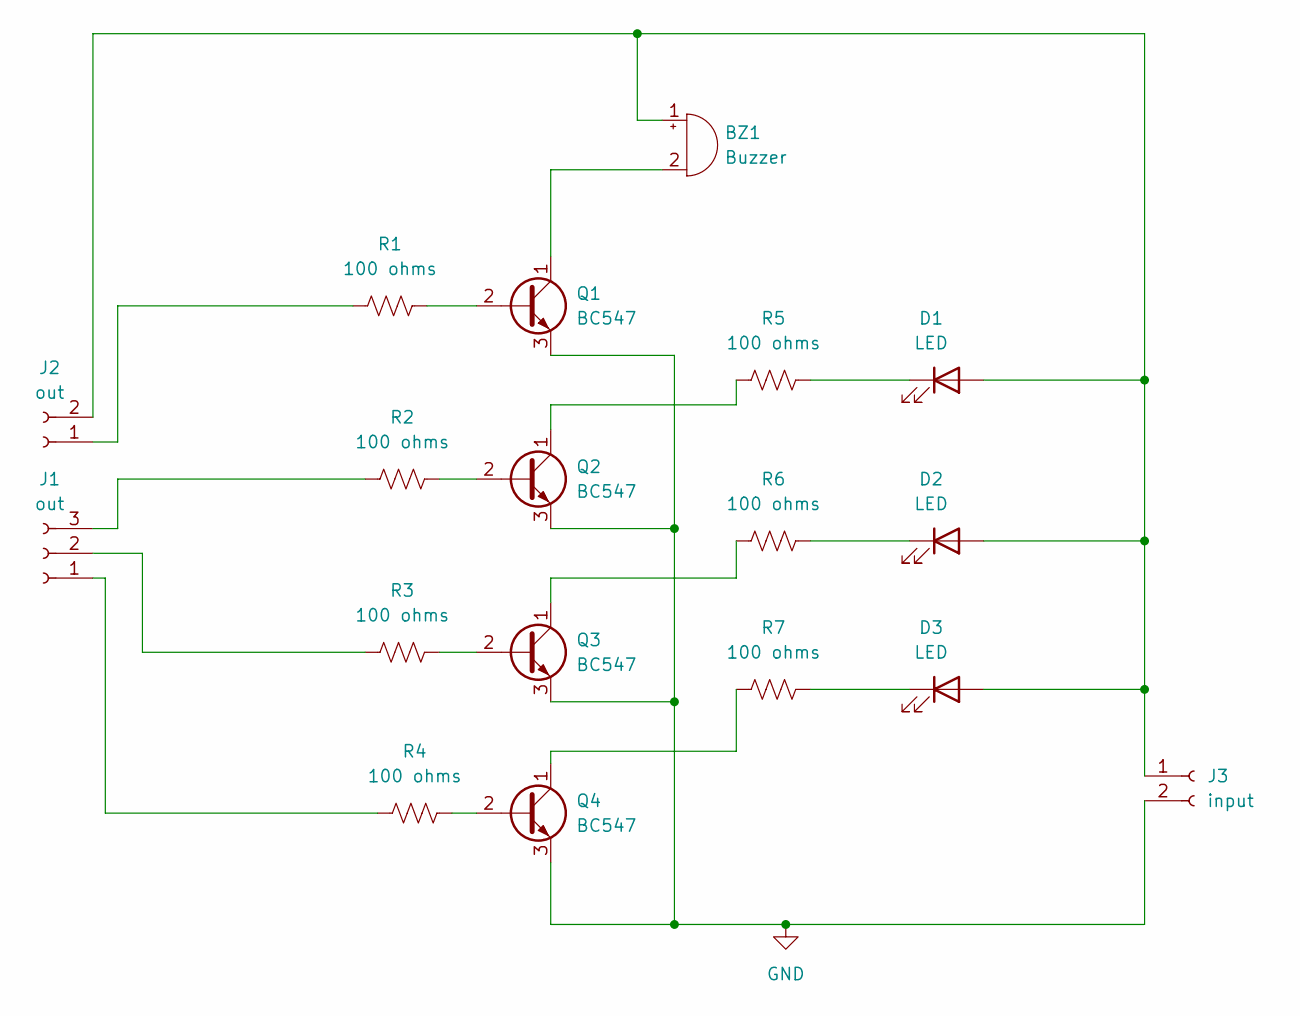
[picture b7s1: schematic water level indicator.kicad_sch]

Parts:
BZ1: Buzzer; Buzzer_15x7.5RM7.6
D1, D2, D3: LED; LED_D3.0mm
J1: out; TerminalBlock_Phoenix_MKDS-1,5-3-5.08_1x03_P5.08mm_Horizont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
J2: out; TerminalBlock_Phoenix_MKDS-1,5-2_1x02_P5.00mm_Horizontal
J3: input; TerminalBlock_Phoenix_MKDS-1,5-2_1x02_P5.00mm_Horizontal
Q1, Q2, Q3, Q4: BC547; TO-92_Inline
R1, R2, R3, R4, R5, R6, R7: 100 ohms; R_Axial_DIN0207_L6.3mm_D2.5mm_P7.62mm_Horizontal

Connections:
GND: J3.2, Q1.3 (E), Q2.3 (E), Q3.3 (E), Q4.3 (E)
unnamed: BZ1.1 (+), D1.2 (A), D2.2 (A), D3.2 (A), J2.2, J3.1
unnamed: BZ1.2 (-), Q1.1 (C)
unnamed: D1.1 (K), R5.2
unnamed: D2.1 (K), R6.2
unnamed: D3.1 (K), R7.2
unnamed: J1.1, R4.1
unnamed: J1.2, R3.1
unnamed: J1.3, R2.1
unnamed: J2.1, R1.1
unnamed: Q1.2 (B), R1.2
unnamed: Q2.2 (B), R2.2
unnamed: Q2.1 (C), R5.1
unnamed: Q3.2 (B), R3.2
unnamed: Q3.1 (C), R6.1
unnamed: Q4.2 (B), R4.2
unnamed: Q4.1 (C), R7.1

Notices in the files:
README.md:
License:
Current project-authored ZapTrace source code is available under the [PolyForm Noncommercial License 1.0.0](LICENSE). Commercial use requires a separate written license from the copyright holder; see [COMMERCIAL-LICENSING.md](COMMERCIAL-LICENSING.md) and [LICENSING.md](LICENSING.md).
Earlier versions and revisions already released under MIT remain available under the MIT terms that applied when they were published. Third-party material keeps its own license terms.
License: PolyForm Noncommercial 1.0.0
